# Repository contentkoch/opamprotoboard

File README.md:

# opamprotoboard
Small prototyping PCBs for building operational amplifier circuits

Off the top of my head possible circuits:

1. feedback loop customizable (adding "veroboard holes")

2. high/low pass 2nd/1st order

3. inverting amp

4. non inverting amp

5. voltage follower

6. summing amplifier

7. differnetial amplifier

8. Real or virtual ground through jumper

9. intergrator

10. differentiator

11. current/voltage converter

12. negative resistance circuit
<p align="center">

  # SMD Version (40mm x 80mm)

  # DIP Version with THT resistors and 5mm pitch capacitors:
  
  (40mm x 100mm)
  This is autorouted (but handplaced), so it is a bit messy. Feel free to improve the design and send it back to me.

</p>

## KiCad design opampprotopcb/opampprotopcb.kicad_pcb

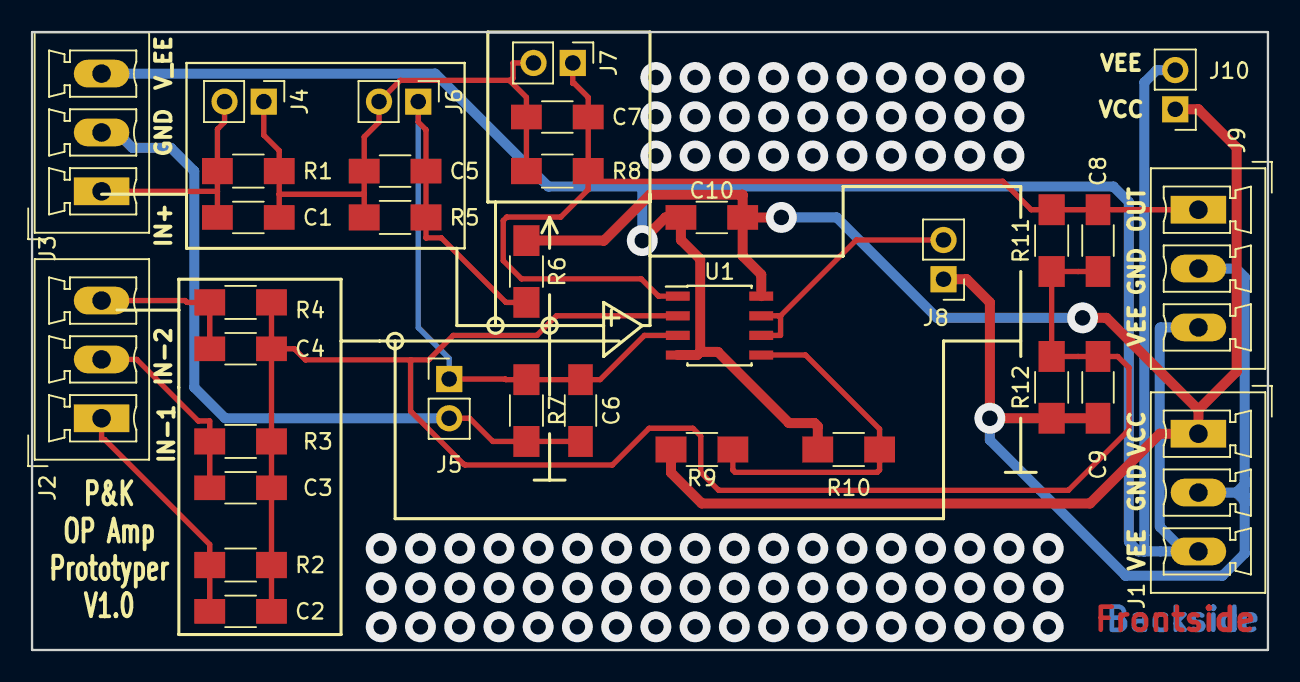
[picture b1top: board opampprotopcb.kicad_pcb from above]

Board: 2 copper layers, 80.0 x 40.0 mm, 33 parts (0 on the bottom side), 13 nets.

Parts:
C1, C2, C3, C4, C5, C6, C7, C8, C9, C10: C; C_1206_HandSoldering
J1, J2, J3, J9: Conn_01x03_Male; PhoenixContact_MCV-G_03x3.81mm_Vertical
J4, J5, J6, J7, J8, J10: Conn_01x02_Male; Pin_Header_Straight_1x02_Pitch2.54mm
R1, R2, R3, R4, R5, R6, R7, R8, R9, R10, R11, R12: R; R_1206_HandSoldering
U1: NE5532; SOIC-8_3.9x4.9mm_Pitch1.27mm

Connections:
GND: C6.1, C9.2, J1.2, J3.2, J5.2, J8.1, J9.2, R7.1, R12.1
INV_In1: C2.2, J2.1, R2.2
N_INV_In: C1.1, J3.1, J4.2, R1.2
unnamed: C1.2, C5.1, C7.1, J4.1, J6.2, J7.2, R1.1, R5.2, R8.2
unnamed: C2.1, C3.1, C4.1, C8.2, C9.1, R2.1, R3.1, R4.1, R11.1, R12.2, U1.2
unnamed: C3.2, J2.2, R3.2
unnamed: C4.2, J2.3, R4.2
unnamed: C5.2, C6.2, J5.1, J6.1, R5.1, R6.1, R7.2, U1.3
unnamed: J8.2, U1.6, U1.7
unnamed: R9.1, R10.2, U1.5
OUTPUT: C7.2, C8.1, J7.1, J9.1, R8.1, R11.2, U1.1
VCC: C10.2, J1.1, J10.1, R6.2, R9.2, U1.8
VEE: C10.1, J1.3, J3.3, J9.3, J10.2, R10.1, U1.4

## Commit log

2019-09-20 SMD Version of the prototyping board; KICAD files including gerber files
2019-09-28 Add files via upload
    DIL Version with hand placement but autorouted.....
2019-09-28 Update README.md
    changed formatting on readme
